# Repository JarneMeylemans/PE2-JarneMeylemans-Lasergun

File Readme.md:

# Practice Enterprise 2: Lasergun

Jarne Meylemans 

(Finale code staat onder 'Project_Code/STM32F4/PE_LASERGUN_CODE_2apr')

## Korte Beschrijving

Het doel van dit project zal zijn te weten komen hoe een lasergun kan werken. Het geweer zal moeten kunnen een infrarood signaal sturen waarmee het bekend maakt wie het is (Elk geweer heeft zo zijn eigen "code". Elke Lasergun zal met een centraal punt kunnen communiceren om een score bij te houden van het houdige spelletje. 

Via een scherm kan de speler zien hoeveel kogels hij nog heeft en wat zijn score is in het spel. 

## Hardware

Om het lasergeweer te maken heb ik gekozen om met de STM32F410 microcontroller te werken, deze stuurt alles aan als volgt: 

## Software 

Met de software heb ik geprobeerd om een soort State Machine te programmeren zodat er makkelijk kan veranderd worden van functie waar we inzitten

## Behuizing

De behuizing is getekend in fusion 360 en is geprint met een 3D printer, de behuizing bestaat uit 11 verschillende stukken.

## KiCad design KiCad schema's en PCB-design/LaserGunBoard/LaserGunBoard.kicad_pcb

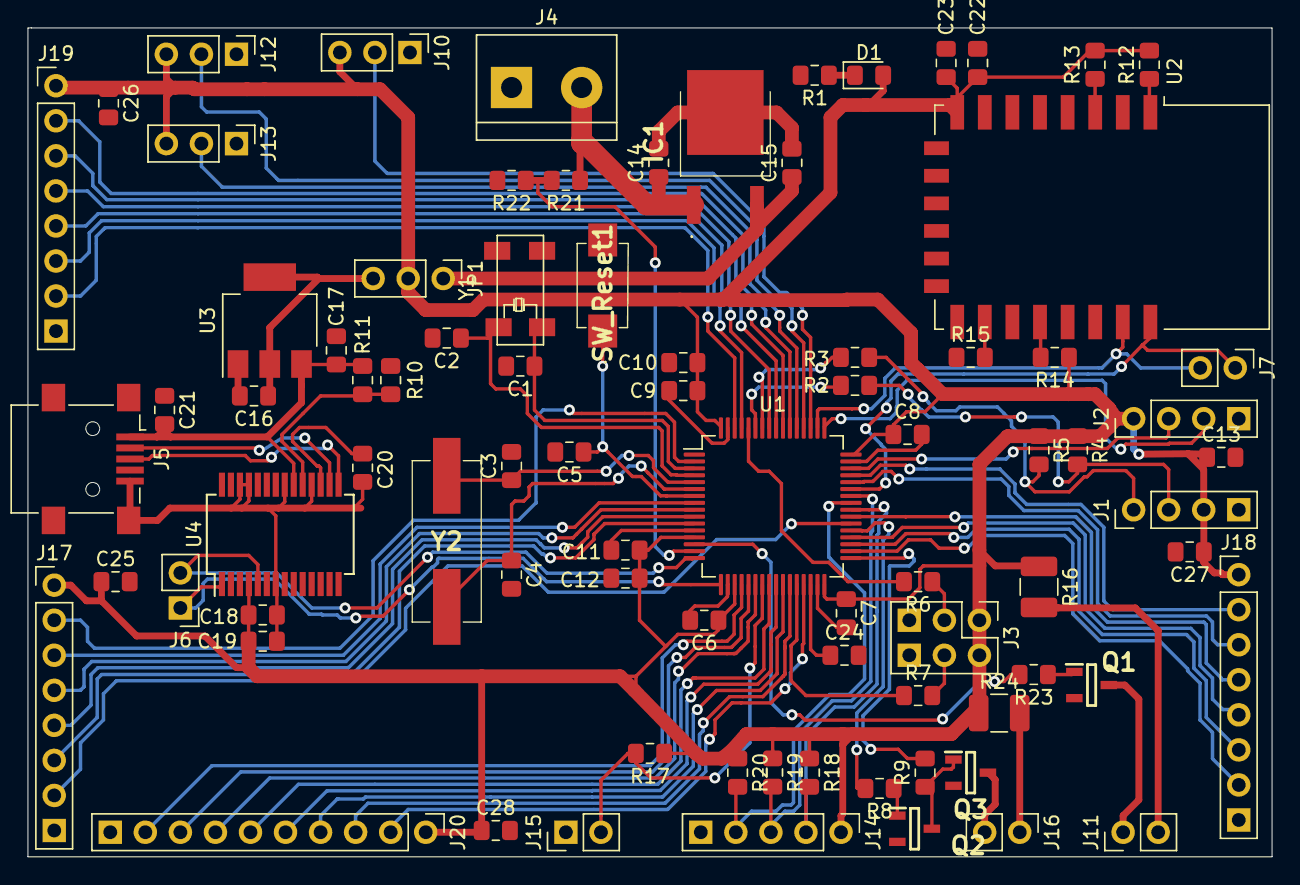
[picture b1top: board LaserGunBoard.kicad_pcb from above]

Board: 2 copper layers, 90.2 x 60.1 mm, 83 parts (0 on the bottom side), 79 nets.

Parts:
C1, C2, C3, C4: 10pF; C_0805_2012Metric_Pad1.15x1.40mm_HandSolder
C5, C15: 0.1µF; C_0805_2012Metric_Pad1.15x1.40mm_HandSolder
C6, C7, C8, C9, C13, C18, C20, C23, C25, C26, C27, C28: 100nF; C_0805_2012Metric_Pad1.15x1.40mm_HandSolder
C10, C19: 4.7µF; C_0805_2012Metric_Pad1.15x1.40mm_HandSolder
C11, C21: 10nF; C_0805_2012Metric_Pad1.15x1.40mm_HandSolder
C12: 1µF; C_0805_2012Metric_Pad1.15x1.40mm_HandSolder
C14: 0.33µF; C_0805_2012Metric_Pad1.15x1.40mm_HandSolder
C16: 47µF; C_0805_2012Metric_Pad1.15x1.40mm_HandSolder
C17, C22: 10µF; C_0805_2012Metric_Pad1.15x1.40mm_HandSolder
C24: 4.7µ; C_0805_2012Metric_Pad1.15x1.40mm_HandSolder
D1: PowerLed; LED_0805_2012Metric_Pad1.15x1.40mm_HandSolder
IC1: UA78M33IKVURG3
J1: 1x4 Male Connector I2C->LCD; PinHeader_1x04_P2.54mm_Vertical
J2: ST-LINK; PinHeader_1x04_P2.54mm_Vertical
J3: BootPins; PinHeader_2x03_P2.54mm_Vertical
J4: Lipo Connectie; TerminalBlock_bornier-2_P5.08mm
J5: USB_B_Mini; USB_Mini-B_Lumberg_2486_01_Horizontal
J6: DebugRX_TX; PinHeader_1x02_P2.54mm_Vertical
J7: ESPRX_TX; PinHeader_1x02_P2.54mm_Vertical
J10: IR_REC1; PinHeader_1x03_P2.54mm_Vertical
J11: LED; PinHeader_1x02_P2.54mm_Vertical
J12: IR_REC2; PinHeader_1x03_P2.54mm_Vertical
J13: IR_REC3; PinHeader_1x03_P2.54mm_Vertical
J14: Rotary Encoder; PinHeader_1x05_P2.54mm_Vertical
J15: Trigger; PinHeader_1x02_P2.54mm_Vertical
J16: IRLED; PinHeader_1x02_P2.54mm_Vertical
J17, J18, J19: Conn_01x08; PinHeader_1x08_P2.54mm_Vertical
J20: Conn_01x10; PinHeader_1x10_P2.54mm_Vertical
JP1: Jumper_NC_Dual; PinHeader_1x03_P2.54mm_Vertical
Q1, Q2, Q3: AC847CWQ-7; SOT95P282X130-3N
R1: 470; R_0805_2012Metric_Pad1.15x1.40mm_HandSolder
R2, R3: 100; R_0805_2012Metric_Pad1.15x1.40mm_HandSolder
R4, R5: 4.7k; R_0805_2012Metric_Pad1.15x1.40mm_HandSolder
R6, R7, R22: 100k; R_0805_2012Metric_Pad1.15x1.40mm_HandSolder
R8, R9, R18, R19, R20, R23: 1k; R_0805_2012Metric_Pad1.15x1.40mm_HandSolder
R10: 4k7; R_0805_2012Metric_Pad1.15x1.40mm_HandSolder
R11, R12, R13, R14, R15, R17: 10k; R_0805_2012Metric_Pad1.15x1.40mm_HandSolder
R16: 100; R_1210_3225Metric_Pad1.42x2.65mm_HandSolder
R21: 330k; R_0805_2012Metric_Pad1.15x1.40mm_HandSolder
R24: 18; R_1210_3225Metric_Pad1.42x2.65mm_HandSolder
SW_Reset1: SW_Push; PTS636SM25FSMTRLFS
U1: STM32F410RBTx; LQFP-64_10x10mm_P0.5mm
U2: ESP-12E
U3: AMS1117-3.3; SOT-223-3_TabPin2
U4: FT232RL; SSOP-28_5.3x10.2mm_P0.65mm
Y1: 32.768KHz; 32-768kHzLOWFrequencySMDcrystal
Y2: 8MHz; FOXSDLF08020

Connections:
+3V3: C6.1, C7.1, C8.1, C9.1, C10.1, C11.1, C12.1, C13.1, C18.1, C19.1, C22.1, C23.1, C25.1, C26.1, C27.1, C28.1, D1.2, J1.3, J2.1, J3.1, J3.2, J10.3, J12.3, J13.3, J14.1, J17.1, J18.1, J19.1, J20.1, JP1.2, R4.1, R5.1, R12.2, R13.2, R14.1, R16.1, R17.1, R18.1, R19.1, R20.1, R24.1, U1.13, U1.19, U1.32, U1.48, U1.64, U2.8, U4.4
+5V: C17.1, C21.1, J5.1, R10.1, U3.3, U4.20
BAT_ADC: R21.2, R22.1, U1.15
BOOT0: R6.2, U1.60
BOOT1: R7.1, U1.28
D+: J5.3, U4.15
D-: J5.2, U4.16
GND: C1.2, C2.2, C3.2, C4.2, C5.2, C6.2, C7.2, C8.2, C9.2, C10.2, C11.2, C12.2, C13.2, C14.2, C15.2, C16.2, C17.2, C18.2, C19.2, C20.1, C21.2, C22.2, C23.2, C24.2, C25.2, C26.2, C27.2, C28.2, IC1.4, J1.4, J2.4, J3.5, J3.6, J4.1, J5.5, J5.6, J10.1, J12.1, J13.1, J14.5, J15.1, J17.8, J18.8, J19.8, J20.10, Q1.2, Q2.2, Q3.2, R1.2, R11.2, R15.1, R22.2, SW_Reset1.2, U1.12, U1.18, U1.31, U1.47, U1.63, U2.15, U3.1, U4.7, U4.18, U4.21, U4.25, U4.26
I2C_SCL: R3.2, U1.58
I2C_SDA: R2.2, U1.59
IR_REC1: J10.2, U1.51
IR_REC2: J12.2, U1.52
IR_REC3: J13.2, U1.53
unnamed: C1.1, U1.3, Y1.1
unnamed: C2.1, U1.4, Y1.2
unnamed: C3.1, U1.5, Y2.1
unnamed: C4.1, U1.6, Y2.2
unnamed: C5.1, SW_Reset1.1, U1.7
unnamed: C15.1, IC1.3, JP1.1
unnamed: C16.1, JP1.3, U3.2
unnamed: C20.2, U4.17
unnamed: C24.1, U1.30
unnamed: D1.1, R1.1
unnamed: J3.3, R6.1
unnamed: J3.4, R7.2
unnamed: J11.1, Q1.3
unnamed: J11.2, R16.2
unnamed: J16.1, R24.2
unnamed: J16.2, Q3.3
unnamed: Q1.1, R23.1
unnamed: Q2.1, R8.1
unnamed: Q2.3, Q3.1, R9.1
unnamed: R10.2, R11.1, U4.19
unnamed: R12.1, U2.1
unnamed: R13.1, U2.3
unnamed: R14.2, U2.18
unnamed: R15.2, U2.16
PA4: J20.9, U1.20
PA5: J20.8, U1.21
PA6: J20.7, U1.22
PA11: J18.3, U1.44
PA12: J18.2, U1.45
PB0: J20.4, U1.26
PB1: J20.3, U1.27
PB3: J19.3, U1.55
PB4: J19.4, U1.56
PB5: J19.5, U1.57
PB8: J19.6, U1.61
PB9: J19.7, U1.62
PB10: J20.2, U1.29
PB11: J19.2, U1.54
PB13: J18.7, U1.34
PB14: J18.6, U1.35
PB15: J18.5, U1.36
PC0: J17.3, U1.8
PC1: J17.4, U1.9
PC2: J17.5, U1.10
PC3: J17.6, U1.11
PC4: J20.6, U1.24
PC5: J20.5, U1.25
PC8: J18.4, U1.39
PC13: J17.2, U1.2
PWM_IR: R9.2, U1.33
RED_LED: R23.2, U1.14
ROT_A: J14.4, R20.2, U1.41
ROT_B: J14.3, R19.2, U1.42
ROT_SW: J14.2, R18.2, U1.40
SCL_LCD: J1.1, R3.1, R5.2
SDA_LCD: J1.2, R2.1, R4.2
SWDCLK: J2.3, U1.49
SWDIO: J2.2, U1.46
TRIGGER: J15.2, R17.2, U1.23
USART1_RX: J7.1, U1.43, U2.22
USART1_TX: J7.2, U1.50, U2.21
USART2_RX: J6.1, U1.17, U4.1
USART2_TX: J6.2, U1.16, U4.5
USART6_RX: J17.7, U1.38
USART6_TX: R8.2, U1.37
VLipo: C14.1, IC1.1, J4.2, R21.1

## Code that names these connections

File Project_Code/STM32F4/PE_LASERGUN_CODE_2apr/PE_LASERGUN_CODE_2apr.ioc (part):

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Mcu.Name=STM32F410R(8-B)Tx
Mcu.Package=LQFP64
Mcu.UserName=STM32F410RBTx
PA0-WKUP.GPIOParameters=GPIO_Label
PA0-WKUP.GPIO_Label=RED_LED
PA0-WKUP.Signal=GPIO_Output
PA1.GPIOParameters=GPIO_Label
PA1.GPIO_Label=BAT_ADC
PA1.Signal=ADCx_IN1
PA10.Mode=Asynchronous
PA10.Signal=USART1_RX
PA13.Mode=Serial_Wire
PA13.Signal=SYS_JTMS-SWDIO
PA14.Mode=Serial_Wire
PA14.Signal=SYS_JTCK-SWCLK
PA15.Mode=Asynchronous
PA15.Signal=USART1_TX
PA2.Mode=Asynchronous
PA2.Signal=USART2_TX
PA3.Mode=Asynchronous
PA3.Signal=USART2_RX
PA7.GPIOParameters=GPIO_Label
PA7.GPIO_Label=TRIGGER
PA7.Signal=GPIO_Input
PA8.GPIOParameters=GPIO_Label
PA8.GPIO_Label=ROT_A
PA8.Signal=S_TIM1_CH1
PA9.GPIOParameters=GPIO_Label
PA9.GPIO_Label=ROT_B
PA9.Signal=S_TIM1_CH2
PB12.GPIOParameters=GPIO_Label
PB12.GPIO_Label=PWM38k_IR
PB12.Signal=S_TIM5_CH1
PB6.Mode=I2C
PB6.Signal=I2C1_SCL
PB7.Mode=I2C
PB7.Signal=I2C1_SDA
PC10.GPIOParameters=GPIO_Label
PC10.GPIO_Label=IR_REC1
PC10.Signal=GPIO_Input
PC11.GPIOParameters=GPIO_Label
PC11.GPIO_Label=IR_REC2
PC11.Signal=GPIO_Input
PC12.GPIOParameters=GPIO_Label
PC12.GPIO_Label=IR_REC3
PC12.Signal=GPIO_Input
PC14-OSC32_IN.Mode=LSE-External-Oscillator
PC14-OSC32_IN.Signal=RCC_OSC32_IN
PC15-OSC32_OUT.Mode=LSE-External-Oscillator
PC15-OSC32_OUT.Signal=RCC_OSC32_OUT
PC4.Signal=S_TIM9_CH1
PC6.GPIOParameters=GPIO_Label
PC6.GPIO_Label=UART_IR
PC6.Mode=Asynchronous
PC6.Signal=USART6_TX
PC7.Mode=Asynchronous
PC7.Signal=USART6_RX
PC9.GPIOParameters=GPIO_Label
PC9.GPIO_Label=ROT_SW
PC9.Signal=GPIO_Input
PH0\ -\ OSC_IN.Mode=HSE-External-Oscillator
PH0\ -\ OSC_IN.Signal=RCC_OSC_IN
PH1\ -\ OSC_OUT.Mode=HSE-External-Oscillator
PH1\ -\ OSC_OUT.Signal=RCC_OSC_OUT
RCC.HSE_VALUE=8000000
RCC.SYSCLKFreq_VALUE=100000000
RCC.SYSCLKSource=RCC_SYSCLKSOURCE_PLLCLK
board=custom

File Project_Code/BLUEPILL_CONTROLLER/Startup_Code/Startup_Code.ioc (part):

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Mcu.Name=STM32F103C(8-B)Tx
Mcu.Package=LQFP48
Mcu.UserName=STM32F103C8Tx
PA13.Mode=Serial_Wire
PA13.Signal=SYS_JTMS-SWDIO
PA14.Mode=Serial_Wire
PA14.Signal=SYS_JTCK-SWCLK
PA2.Mode=Asynchronous
PA2.Signal=USART2_TX
PA3.Mode=Asynchronous
PA3.Signal=USART2_RX
PA8.Signal=S_TIM1_CH1
PA9.Signal=S_TIM1_CH2
PB12.GPIOParameters=GPIO_Label
PB12.GPIO_Label=TRIGGER
PB12.Signal=GPIO_Input
PB15.GPIOParameters=GPIO_Label
PB15.GPIO_Label=SW
PB15.Signal=GPIO_Input
PB6.Mode=Asynchronous
PB6.Signal=USART1_TX
PB7.Mode=Asynchronous
PB7.Signal=USART1_RX
PB8.Mode=I2C
PB8.Signal=I2C1_SCL
PB9.Mode=I2C
PB9.Signal=I2C1_SDA
PC13-TAMPER-RTC.GPIOParameters=GPIO_Label
PC13-TAMPER-RTC.GPIO_Label=LED
PC13-TAMPER-RTC.Signal=GPIO_Output
PC14-OSC32_IN.Mode=LSE-External-Oscillator
PC14-OSC32_IN.Signal=RCC_OSC32_IN
PC15-OSC32_OUT.Mode=LSE-External-Oscillator
PC15-OSC32_OUT.Signal=RCC_OSC32_OUT
PD0-OSC_IN.Mode=HSE-External-Oscillator
PD0-OSC_IN.Signal=RCC_OSC_IN
PD1-OSC_OUT.Mode=HSE-External-Oscillator
PD1-OSC_OUT.Signal=RCC_OSC_OUT
RCC.SYSCLKFreq_VALUE=72000000
RCC.SYSCLKSource=RCC_SYSCLKSOURCE_PLLCLK
board=custom

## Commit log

2021-03-06 Aanmaken .gitignore file
2021-03-06 aanmaken van een Readme.md file
2021-03-15 Toevoeging van alle bestanden die te maken hebben met het project
    Toevoeging van:
    -> Documenten (datasheets, foto's, logboek)
    ->KiCad (schema's en PCB designs)
    ->Project_Code (hier komt de code in die het project zal gebruiken)
    -> Test_code (hier staat code in die één voor één verschillende delen van het project gaat testen)
2021-04-08 extra aanvullingen
    - PCB afgewerkt + gesoldeerd
    - code geschreven voor gesoldeerd bordje
    - Afbeeldingen gemaakt voor tijdens het programma te tonen
    -
2021-04-08 Foto's toevoegen
2021-05-22 Update
    alle nieuw geschreven code implementeren als ook de behuizing stl files
2021-05-22 nieuwe readme
    afbeeldingen en extra info in de readme
2021-05-25 code aangepast (heel kleine update)
